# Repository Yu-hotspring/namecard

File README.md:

2024/01/20~21に開催された全国ロボコン交流会で配布した基板名刺です。
※実際に配布したものとは一部異なります

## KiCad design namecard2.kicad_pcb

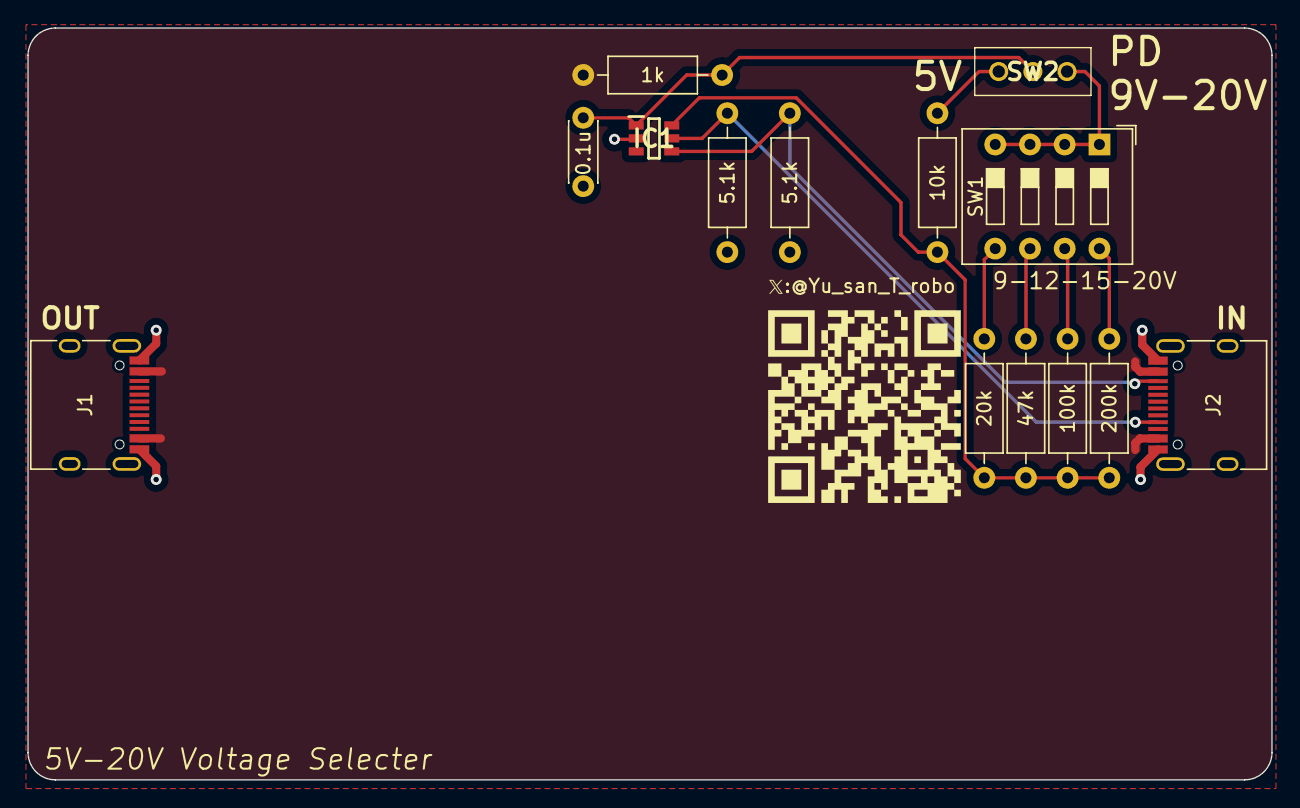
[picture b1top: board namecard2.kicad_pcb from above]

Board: 2 copper layers, 91.0 x 55.0 mm, 14 parts (0 on the bottom side), 12 nets.

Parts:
0.1u: 0.1u; C_Disc_D4.3mm_W1.9mm_P5.00mm
1k: 1k; R_Axial_DIN0207_L6.3mm_D2.5mm_P10.16mm_Horizontal
5.1k, 5.1k#2: 5.1k; R_Axial_DIN0207_L6.3mm_D2.5mm_P10.16mm_Horizontal
10k: 10k; R_Axial_DIN0207_L6.3mm_D2.5mm_P10.16mm_Horizontal
20k: 20k; R_Axial_DIN0207_L6.3mm_D2.5mm_P10.16mm_Horizontal
47k: 47k; R_Axial_DIN0207_L6.3mm_D2.5mm_P10.16mm_Horizontal
100k: 100k; R_Axial_DIN0207_L6.3mm_D2.5mm_P10.16mm_Horizontal
200k: 200k; R_Axial_DIN0207_L6.3mm_D2.5mm_P10.16mm_Horizontal
IC1: CH221K; SOT95P280X120-6N
J1, J2: USB_C_Receptacle_USB2.0; USB_C_Receptacle_HRO_TYPE-C-31-M-12
SW1: SW_DIP_x04; SW_DIP_SPSTx04_Slide_9.78x12.34mm_W7.62mm_P2.54mm
SW2: SW_SPDT; SS12D00G3

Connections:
/100k: 10k.2, 20k.2, 47k.2, 100k.2, 200k.2, IC1.6 (CFG)
/VBUS: 1k.2, J1.A4 (VBUS), J1.A9 (VBUS), J1.B4 (VBUS), J1.B9 (VBUS), J2.A4 (VBUS), J2.A9 (VBUS), J2.B4 (VBUS), J2.B9 (VBUS)
/VDD: 0.1u.1, 1k.1, IC1.1 (VDD), SW2.2 (B)
GND: 0.1u.2, 5.1k.2, 5.1k#2.2, IC1.2 (GND), J1.A1 (GND), J1.A12 (GND), J1.B1 (GND), J1.B12 (GND), J2.A1 (GND), J2.A12 (GND), J2.B1 (GND), J2.B12 (GND)
unnamed: 5.1k#2.1, IC1.4 (CC1), J2.B5 (CC2)
unnamed: 5.1k.1, IC1.5 (CC2), J2.A5 (CC1)
unnamed: 20k.1, SW1.5
unnamed: 47k.1, SW1.6
unnamed: 100k.1, SW1.7
unnamed: 200k.1, SW1.8
unnamed: SW1.1, SW1.2, SW1.3, SW1.4, SW2.1 (A)
unnamed: 10k.1, SW2.3 (C)
